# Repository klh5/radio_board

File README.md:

# radio_board

This board was made so that I could practice using Eagle, and also get some practice soldering SMD components. It consists of an ATMEGA328 and an RFM69 radio. The design is based on the Moteino (http://lowpowerlab.com/moteino/) with an added reset button and pads for an SMA connector for the antenna. You tend to get better range using just a wire antenna but they aren't very robust.

I have soldered one of these and it does work, though as the footprint is much bigger than a Moteino or Anarduino it is really only useful as practice, or as a basis for other designs.

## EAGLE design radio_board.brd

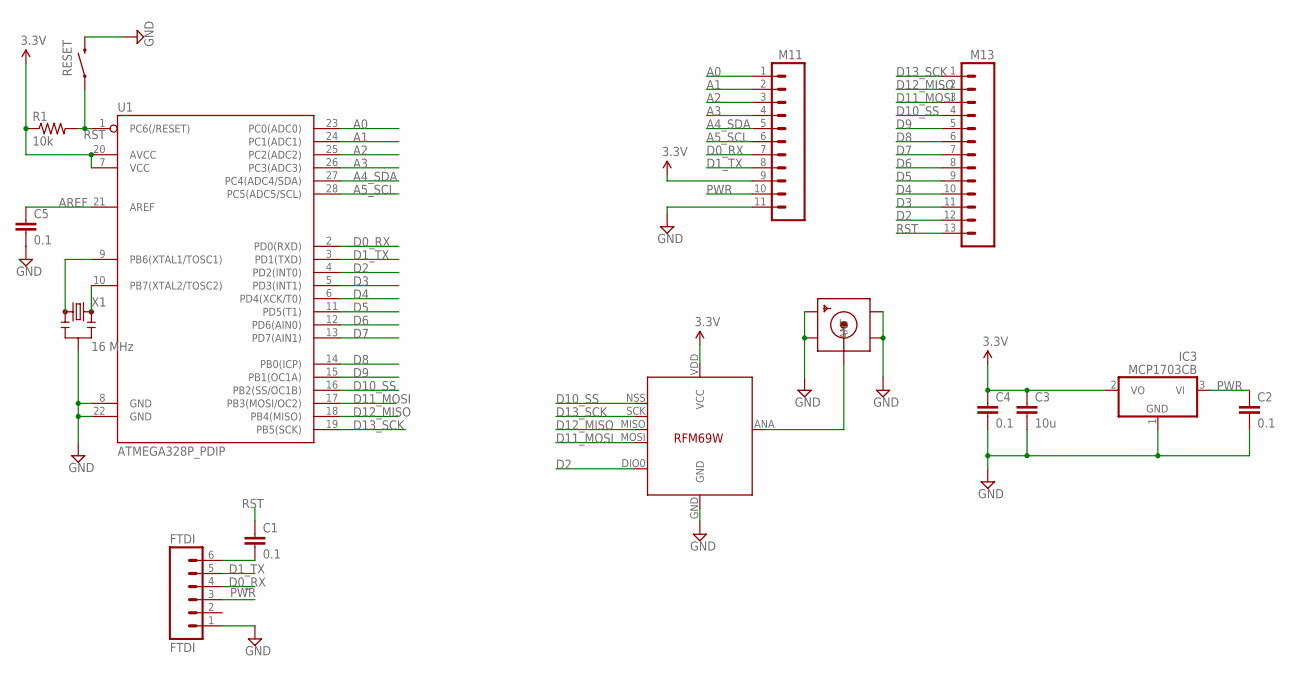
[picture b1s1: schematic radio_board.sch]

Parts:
C1, C2, C4, C5: 0.1; CAP-PTH-SMALL
C3: 10u; CAP-PTH-SMALL
DIGITALSIDE: M13; 1X13
FTDI: FTDI; 1X06
IC3: MCP1703CB; SOT23
M11: M11PTH; 1X11
R1: 10k; AXIAL-0.4
RESET: SWITCH-MOMENTARY-2SMD; TACTILE-SWITCH-SMD
SMA_CONNECTOR: SMACONNECTOR_EDGE; SMA_EDGELAUNCH
U1: ATMEGA328P_PDIP; DIL28-3
U$5: RFM69HW; RFM69W-MINPADS
X1: 16 MHz; RESONATOR-PTH

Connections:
A0: M11.1, U1.23 (PC0(ADC0))
A1: M11.2, U1.24 (PC1(ADC1))
A2: M11.3, U1.25 (PC2(ADC2))
A3: M11.4, U1.26 (PC3(ADC3))
A4_SDA: M11.5, U1.27 (PC4(ADC4/SDA))
A5_SCL: M11.6, U1.28 (PC5(ADC5/SCL))
ANT: SMA_CONNECTOR.P (ANT), U$5.ANA (ANT)
AREF: C5.1, U1.21 (AREF)
D0_RX: FTDI.4, M11.7, U1.2 (PD0(RXD))
D1_TX: FTDI.5, M11.8, U1.3 (PD1(TXD))
D2: DIGITALSIDE.12, U1.4 (PD2(INT0)), U$5.DIO0
D3: DIGITALSIDE.11, U1.5 (PD3(INT1))
D4: DIGITALSIDE.10, U1.6 (PD4(XCK/T0))
D5: DIGITALSIDE.9, U1.11 (PD5(T1))
D6: DIGITALSIDE.8, U1.12 (PD6(AIN0))
D7: DIGITALSIDE.7, U1.13 (PD7(AIN1))
D8: DIGITALSIDE.6, U1.14 (PB0(ICP))
D9: DIGITALSIDE.5, U1.15 (PB1(OC1A))
D10_SS: DIGITALSIDE.1, U1.16 (PB2(SS/OC1B)), U$5.NSS (SEL)
D11_MOSI: DIGITALSIDE.2, U1.17 (PB3(MOSI/OC2)), U$5.MOSI
D12_MISO: DIGITALSIDE.3, U1.18 (PB4(MISO)), U$5.MISO
D13_SCK: DIGITALSIDE.4, U1.19 (PB5(SCK)), U$5.SCK
GND: C2.2, C3.2, C4.2, C5.2, FTDI.1, IC3.1 (GND), M11.11, RESET.3 (2), SMA_CONNECTOR.GND@1 (GND4), SMA_CONNECTOR.GND@2 (GND3), SMA_CONNECTOR.GND@3 (GND2), SMA_CONNECTOR.GND@4 (GND1), U1.8 (GND), U1.22 (GND), U$5.GND, X1.2
unnamed: U1.9 (PB6(XTAL1/TOSC1)), X1.1
unnamed: C1.2, FTDI.6
unnamed: U1.10 (PB7(XTAL2/TOSC2)), X1.3
PWR: C2.1, FTDI.3, IC3.3 (VI), M11.10
RST: C1.1, DIGITALSIDE.13, R1.P$2 (2), RESET.1, U1.1 (PC6(/RESET))
VCC: C3.1, C4.1, IC3.2 (VO), M11.9, R1.P$1 (1), U1.7 (VCC), U1.20 (AVCC), U$5.VDD (VCC)

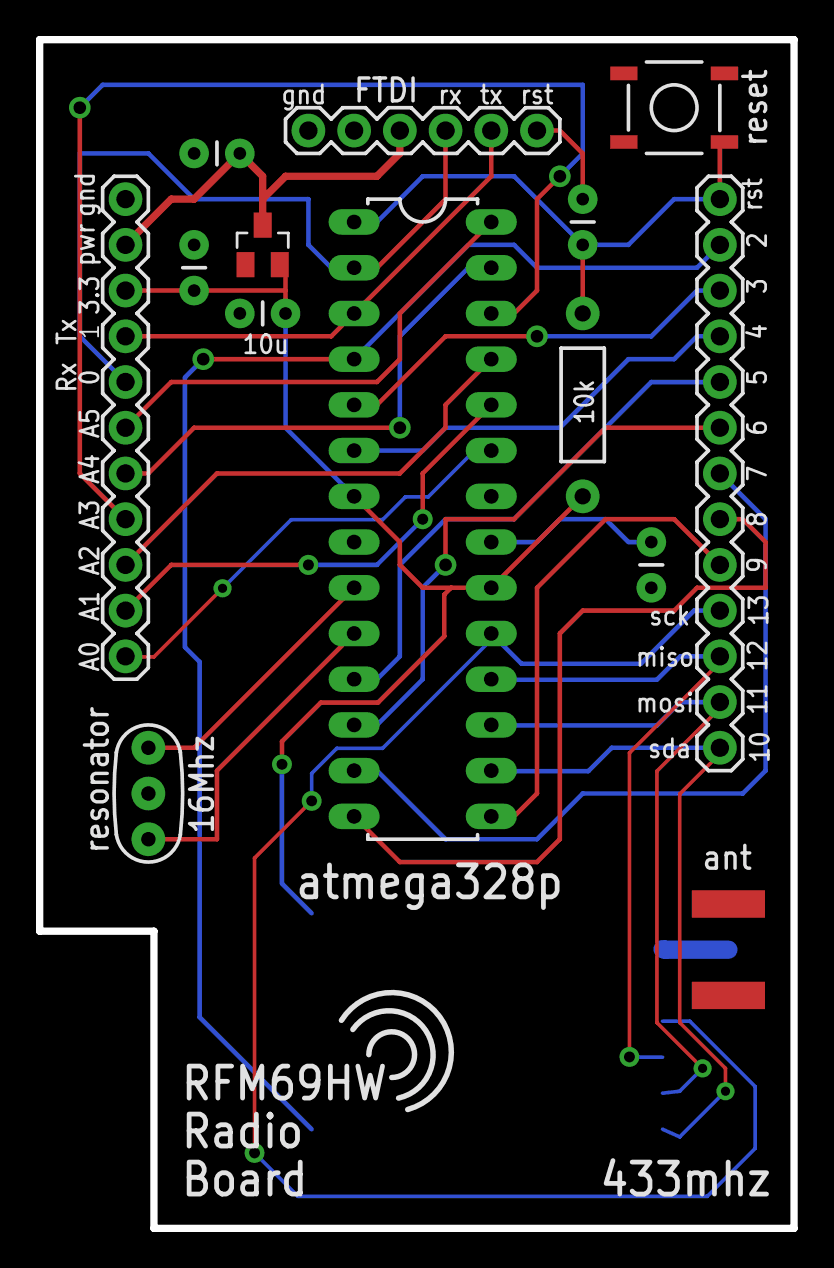
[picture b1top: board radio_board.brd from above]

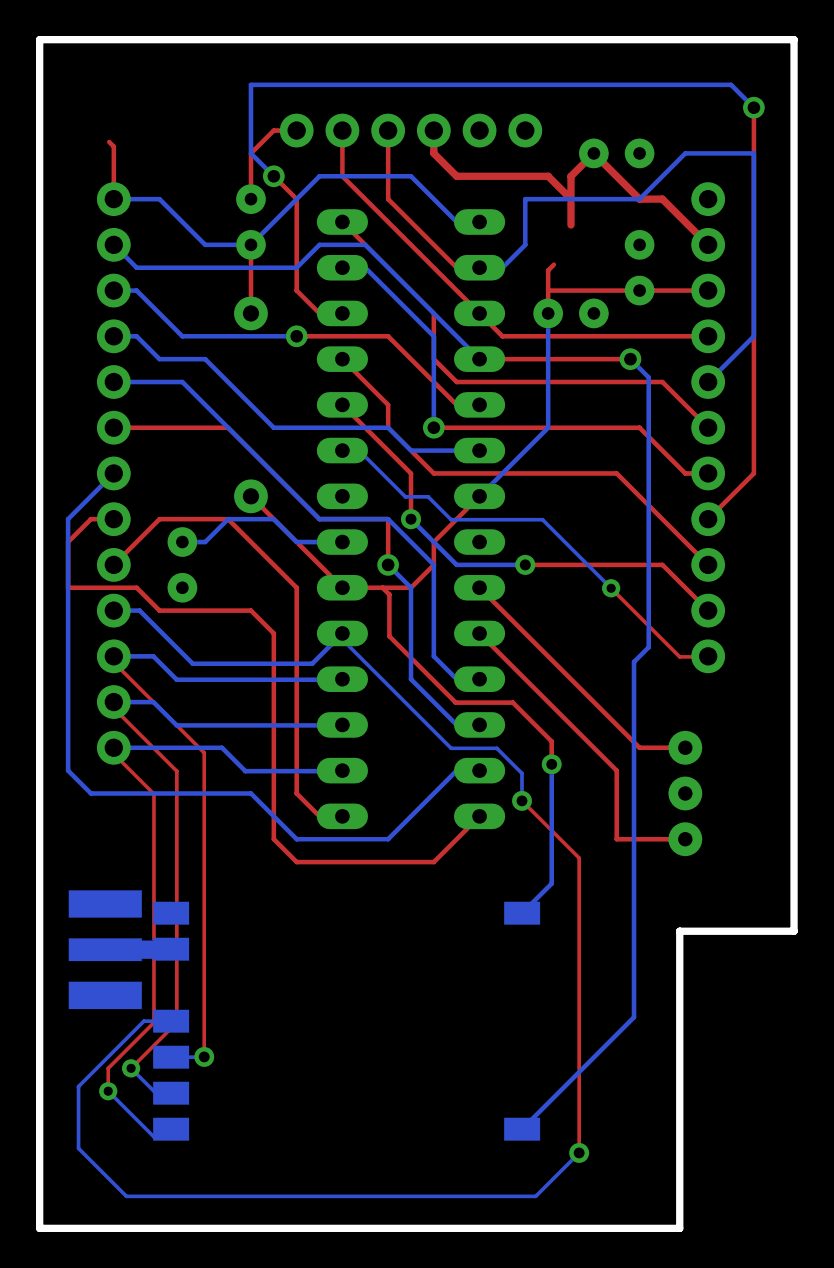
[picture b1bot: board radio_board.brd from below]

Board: 2 copper layers, 41.9 x 66.0 mm, 15 parts (2 on the bottom side), 29 nets.

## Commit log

2016-07-05 Adding README
2016-07-05 Adding detail to README
2016-07-05 Adding Eagle design files
2016-07-05 Adding picture
2016-07-05 Adding gerber files
2016-07-15 Adding link to image

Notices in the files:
parts and their libraries:
SparkFun-FreqCtrl: Licensing: Creative Commons ShareAlike 4.0 International - https://creativecommons.org/licenses/by-sa/4.0
SparkFun-Connectors: Licensing: CC v3.0 Share-Alike You are welcome to use this library for commercial purposes.
